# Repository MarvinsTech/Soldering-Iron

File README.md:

# Soldering-Iron

### Required parts
* 1x [Soldering iron PCB](https://github.com/MarvinsTech/Soldering-Iron/tree/master/Eagle%20file/Soldering%20Iron%20V2/GerberFile.zip)
(To order the PCB, visit https://jlcpcb.com)
* 1x [ATmega328pAU](https://de.aliexpress.com/item/32900110997.html?spm=a2g0o.productlist.0.0.6260378blZ3Cgl&algo_pvid=3a814b0d-65b6-42ce-b419-f9f72c1997d7&algo_expid=3a814b0d-65b6-42ce-b419-f9f72c1997d7-30&btsid=363c362b-cf80-4f91-8e9c-2e44274fab52&ws_ab_test=searchweb0_0,searchweb201602_4,searchweb201603_53)
* 1x [Female DC power jack](https://de.aliexpress.com/item/1000007253624.html?spm=a2g0o.productlist.0.0.63461dcaoJZtV4&algo_pvid=28c6eaf7-739f-4408-a783-d572ee06ba7d&algo_expid=28c6eaf7-739f-4408-a783-d572ee06ba7d-13&btsid=e61eab79-1ec7-4b98-b4ed-ceea8f2bdb99&ws_ab_test=searchweb0_0,searchweb201602_4,searchweb201603_53)
* 1x [16MHz SMD crystal](https://de.aliexpress.com/item/32451311354.html?spm=a2g0o.productlist.0.0.955d2071jGW3XO&algo_pvid=27d65776-a1d2-4b0c-b73d-df3cc9d4dbca&algo_expid=27d65776-a1d2-4b0c-b73d-df3cc9d4dbca-0&btsid=ab6a54f6-5959-48a4-89e6-ce26026505f9&ws_ab_test=searchweb0_0,searchweb201602_4,searchweb201603_53)
* 1x [SS12 Schottky diode](https://de.aliexpress.com/item/32904408053.html?spm=a2g0o.productlist.0.0.e1dd669c1vQRey&algo_pvid=b6082e91-097d-48c2-a7c7-d61494ba035c&algo_expid=b6082e91-097d-48c2-a7c7-d61494ba035c-2&btsid=abe08064-b50d-44c2-9e66-502e07728063&ws_ab_test=searchweb0_0,searchweb201602_4,searchweb201603_53)
* 1x [2SC3356 R25 SOT-23](https://de.aliexpress.com/item/32895374766.html?spm=a2g0s.9042311.0.0.27424c4daI4iIC)
* 2x [1kΩ SMD Resistor](https://de.aliexpress.com/item/32865947306.html?spm=a2g0o.productlist.0.0.61063a32Yrv3OQ&algo_pvid=bcb79219-ee75-488c-8d39-fa32f1db371b&algo_expid=bcb79219-ee75-488c-8d39-fa32f1db371b-2&btsid=52a44622-5dbe-44f4-860e-663f6887a7ad&ws_ab_test=searchweb0_0,searchweb201602_4,searchweb201603_53)
* 5x [10kΩ SMD Resistor](https://de.aliexpress.com/item/32865947306.html?spm=a2g0o.productlist.0.0.61063a32Yrv3OQ&algo_pvid=bcb79219-ee75-488c-8d39-fa32f1db371b&algo_expid=bcb79219-ee75-488c-8d39-fa32f1db371b-2&btsid=52a44622-5dbe-44f4-860e-663f6887a7ad&ws_ab_test=searchweb0_0,searchweb201602_4,searchweb201603_53)
* 1x [1MΩ SMD Resistor](https://de.aliexpress.com/item/32865947306.html?spm=a2g0o.productlist.0.0.61063a32Yrv3OQ&algo_pvid=bcb79219-ee75-488c-8d39-fa32f1db371b&algo_expid=bcb79219-ee75-488c-8d39-fa32f1db371b-2&btsid=52a44622-5dbe-44f4-860e-663f6887a7ad&ws_ab_test=searchweb0_0,searchweb201602_4,searchweb201603_53)
* 1x [200kΩ SMD Resistor](https://de.aliexpress.com/item/32865947306.html?spm=a2g0o.productlist.0.0.61063a32Yrv3OQ&algo_pvid=bcb79219-ee75-488c-8d39-fa32f1db371b&algo_expid=bcb79219-ee75-488c-8d39-fa32f1db371b-2&btsid=52a44622-5dbe-44f4-860e-663f6887a7ad&ws_ab_test=searchweb0_0,searchweb201602_4,searchweb201603_53)
* 2x [5kΩ SMD Resistor](https://de.aliexpress.com/item/32865947306.html?spm=a2g0o.productlist.0.0.61063a32Yrv3OQ&algo_pvid=bcb79219-ee75-488c-8d39-fa32f1db371b&algo_expid=bcb79219-ee75-488c-8d39-fa32f1db371b-2&btsid=52a44622-5dbe-44f4-860e-663f6887a7ad&ws_ab_test=searchweb0_0,searchweb201602_4,searchweb201603_53)
* 1x [100KΩ SMD Resistor](https://de.aliexpress.com/item/32865947306.html?spm=a2g0o.productlist.0.0.61063a32Yrv3OQ&algo_pvid=bcb79219-ee75-488c-8d39-fa32f1db371b&algo_expid=bcb79219-ee75-488c-8d39-fa32f1db371b-2&btsid=52a44622-5dbe-44f4-860e-663f6887a7ad&ws_ab_test=searchweb0_0,searchweb201602_4,searchweb201603_53)
* 3x [71Ω SMD Resistor](https://de.aliexpress.com/item/32865947306.html?spm=a2g0o.productlist.0.0.61063a32Yrv3OQ&algo_pvid=bcb79219-ee75-488c-8d39-fa32f1db371b&algo_expid=bcb79219-ee75-488c-8d39-fa32f1db371b-2&btsid=52a44622-5dbe-44f4-860e-663f6887a7ad&ws_ab_test=searchweb0_0,searchweb201602_4,searchweb201603_53)
* 1x [2,2nF SMD Capacitor](https://de.aliexpress.com/item/33016966236.html?spm=a2g0o.productlist.0.0.6c6b60b4tVU0MR&algo_pvid=03d69282-82e0-42e8-bb2c-220880516333&algo_expid=03d69282-82e0-42e8-bb2c-220880516333-7&btsid=f46463b0-f910-4c0b-bc69-396dcb17054b&ws_ab_test=searchweb0_0,searchweb201602_4,searchweb201603_53)
* 3x [100nF/0,1uF SMD Capacitor](https://de.aliexpress.com/item/33016966236.html?spm=a2g0o.productlist.0.0.6c6b60b4tVU0MR&algo_pvid=03d69282-82e0-42e8-bb2c-220880516333&algo_expid=03d69282-82e0-42e8-bb2c-220880516333-7&btsid=f46463b0-f910-4c0b-bc69-396dcb17054b&ws_ab_test=searchweb0_0,searchweb201602_4,searchweb201603_53)
* 3x [PCB Fuse clip](https://de.aliexpress.com/item/32804593991.html?spm=a2g0s.9042311.0.0.27424c4daI4iIC)
* 1x [LM358 LM358DR SOP8](https://de.aliexpress.com/item/32418758151.html?spm=a2g0s.9042311.0.0.27424c4daI4iIC)
* 2x [90° SMD Side push button](https://de.aliexpress.com/item/32876437017.html?spm=a2g0s.9042311.0.0.27424c4daI4iIC)
* 1x [Vibrate sensor SW-18015P](https://de.aliexpress.com/item/32954698373.html?spm=a2g0s.9042311.0.0.27424c4dcR7Mjv)
* 1x [I2C OLED 128x32](https://de.aliexpress.com/item/32794583827.html?spm=a2g0s.9042311.0.0.27424c4dJZC5U3)
* 1x [IRF4905S MOSFET](https://de.aliexpress.com/item/32907696197.html?spm=a2g0o.productlist.0.0.2aca5827929ltt&algo_pvid=988ff981-e189-4f43-9fdc-09ed36d629c1&algo_expid=988ff981-e189-4f43-9fdc-09ed36d629c1-56&btsid=8798c4df-59c2-4f42-b01b-367349f54644&ws_ab_test=searchweb0_0,searchweb201602_4,searchweb201603_53)
* 1x [RGB LED](https://de.aliexpress.com/item/32384196929.html?spm=a2g0s.9042311.0.0.27424c4dbM3enp)
* 1x USB B cable
* 1x [T12 tip](https://de.aliexpress.com/item/32964816255.html?spm=a2g0o.productlist.0.0.7c286e81WCeorz&algo_pvid=becfe919-1923-47df-bebf-4e86b254c3d0&algo_expid=becfe919-1923-47df-bebf-4e86b254c3d0-1&btsid=428c11f6-3fa4-45bc-bfd0-d114c0837481&ws_ab_test=searchweb0_0,searchweb201602_4,searchweb201603_53)
* 1x [Buck converter 22 * 17 * 5mm](https://de.aliexpress.com/item/32901415443.html?spm=a2g0s.9042311.0.0.27424c4dPg1aoU)
* 1x [FTDI module](https://de.aliexpress.com/item/32826575637.html?spm=a2g0o.productlist.0.0.2ba36b57X6JT8A&algo_pvid=7d64f631-2c61-41ad-a472-009a9779fd66&algo_expid=7d64f631-2c61-41ad-a472-009a9779fd66-0&btsid=e6b133be-f678-48f3-b6a3-1f7580f63944&ws_ab_test=searchweb0_0,searchweb201602_4,searchweb201603_53)
* 1x Heatsink 14 * 14,5 * 4mm
* 4x M2 screws and nuts

### Hints
Note that the two points of the GND bridge are connected with solder!

### Completely soldered example

### Installing the bootloader on ATmega328
Almost all newly purchased ATmega328 microcontrollers lack the boot loader, so we have to install it ourselves. For this we need an Arduino that is connected as shown in the picture (Make sure that all components on the PCB except the display are soldered!). After the ATmega328 is connected to the Arduino via jumper cables, we have to install OptiLoader on the Arduino and see if it does not display an error message in the serial monitor. If no error message appears, the jumper cables can be unsoldered from the ATmega328.

https://github.com/WestfW/OptiLoader

### Load the program onto ATmega328
Before we load the program onto the ATmega328, we first have to implement the FTDI module in the Arduino IDE. To do this, follow the step-by-step instructions below.

* Open the Arduino IDE.
* Open the File > Preferences menu item.
* Enter the following URL in Additional Boards Manager URLs:
`https://mcudude.github.io/MiniCore/package_MCUdude_MiniCore_index.json`
* Open the Tools > Board > Boards Manager... menu item.
* Wait for the platform indexes to finish downloading.
* Scroll down until you see the MiniCore entry and click on it.
* Click Install.

Next we select the ATmega328 board from Tools, connect the FTDI module to the computer and upload the program to the PCB via the FTDI interface.

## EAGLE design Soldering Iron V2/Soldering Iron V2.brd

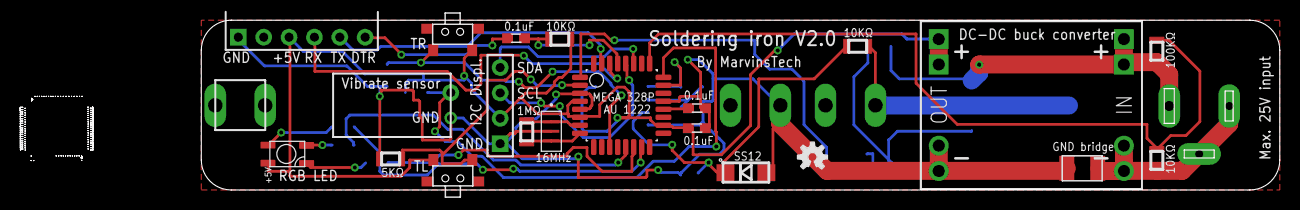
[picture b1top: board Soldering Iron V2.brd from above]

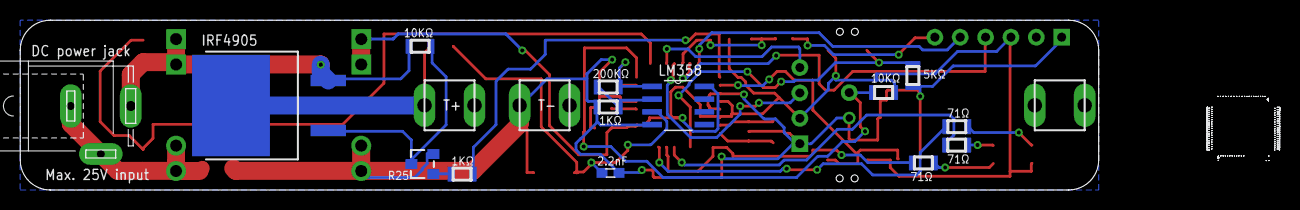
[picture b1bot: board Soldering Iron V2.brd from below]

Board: 2 copper layers, 126.1 x 17.0 mm, 38 parts (14 on the bottom side), 30 nets.

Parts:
C1: 2.2nF; 0603
C2, C3, C4: 0.1uF; 0603
D1: SS12; DO214AC
J1: SPC4077
K1, K2: SMD-BUTTON(2+2P-7X3.5MM-90D); SW4-SMD-7.0X3.5X3.5MM-90D
R1_10KΩ, R2_1KΩ, R3_10KΩ, R4_1KΩ, R5_200KΩ, R6_10KΩ, R7_1MΩ, R8_2KΩ, R9_2KΩ, R10_10KΩ, R11_10KΩ, R12_100KΩ, R13_71Ω, R14_71Ω, R15_71Ω: SMK
U1: LM358M; SOIC127P620X175-8N
U2: ATMEGA328P-AUR; QFP80P900X900X120-32N
U$1: DC-DC-STEP-DOWN-MP1584
U$2: IRF4905STRLPBF; D2PAK-5
U$3: 2SC3356NPNBJT; TO236
U$4: I2C_DISPLAY
U$5: VIBRATESENSOR
U$6, U$7, U$8: FUSECLIPS; FUSECLIP
U$9: SHUNT_RESISTOR1; RESISTOR1
U$10: RGBLED
U$11: PROGRAMMER
U$15: OSHW-LOGOS; OSHW-LOGO-S
Y1: CSTCE16M0V53-R0; OSC_CSTCE16M0V53-R0

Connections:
+5V: C3.2, K1.1, K2.1, R6_10KΩ.2, R10_10KΩ.1, U1.8, U2.4, U2.6, U2.18, U$1.OUT+.1, U$1.OUT+.2, U$4.+5V, U$10.+5V, U$11.+5V
DTR: C2.2, U$11.DTR
GND: C1.2, C3.1, C4.1, D1.A, R4_1KΩ.1, R8_2KΩ.1, R9_2KΩ.1, U1.4, U2.3, U2.5, U2.21, U$1.OUT-.1, U$1.OUT-.2, U$3.P2, U$4.GND, U$5.GND, U$7.P2, U$9.P2, U$11.GND, Y1.2
GNDA: J1.1, J1.2, R11_10KΩ.2, U$1.IN-.1, U$1.IN-.2, U$9.P1
LED_B: R15_71Ω.1, U2.15
LED_G: R13_71Ω.2, U2.13
LED_R: R14_71Ω.2, U2.14
unnamed: R1_10KΩ.2, U$2.P1, U$3.P1
unnamed: R2_1KΩ.2, U$3.P3
unnamed: C4.2, U2.20
unnamed: R7_1MΩ.2, U2.7, Y1.1
unnamed: R7_1MΩ.1, U2.8, Y1.3
unnamed: R14_71Ω.1, U$10.P2
unnamed: R13_71Ω.1, U$10.P3
unnamed: R15_71Ω.2, U$10.P1
PWM_MOS: R2_1KΩ.1, U2.1
RESET: C2.1, R6_10KΩ.1, U2.29
RX: U2.30, U$11.RX
SCL: U2.28, U$4.SCL
SDA: U2.27, U$4.SDA
TEMP: R5_200KΩ.1, U1.1, U2.23
TEMP_SENSE: R3_10KΩ.1, U$2.P3, U$6.P2
TX: U2.31, U$11.TX
T_L: K1.2, R8_2KΩ.2, U2.2
T_R: K2.2, R9_2KΩ.2, U2.11
V+: C1.1, D1.C, R3_10KΩ.2, U1.3
V-: R4_1KΩ.2, R5_200KΩ.2, U1.2
VCC: J1.3, R1_10KΩ.1, R12_100KΩ.2, U$1.IN+.1, U$1.IN+.2, U$2.P2
VIBRATE_SENSOR: R10_10KΩ.2, U2.24, U$5.HALL
VOLTAGE: R11_10KΩ.1, R12_100KΩ.1, U2.25

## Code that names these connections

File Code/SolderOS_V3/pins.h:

#ifndef PINS_H
#define PINS_H

//RGB LED on PCB//

#define LED_B 11 //PWM
#define LED_G 9  //PWM
#define LED_R 10 //PWM

//Buttons extern//

#define ButtonR    7 //no PWM
#define ButtonL    4 //no PWM

//IC2//

#define SDA A4
#define SCL A5

//Buzzer addable//

#define Buzzer 5 //PWM

//Voltage gauge//

#define VoltageGauge A2

//VibrSensor sensor//

#define VibrSensor A1

//Iron temp//

#define IronTemp A0

//MOSFED for soldering iron// 

#define MOSFED 3 //PWM

#endif

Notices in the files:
parts and their libraries:
SMD Cap: Licensing: Creative Commons ShareAlike 4.0 International - https://creativecommons.org/licenses/by-sa/4.0
diy-modules: Released under the Creative Commons Attribution 4.0 International License: http://creativecommons.org/licenses/by/4.0
